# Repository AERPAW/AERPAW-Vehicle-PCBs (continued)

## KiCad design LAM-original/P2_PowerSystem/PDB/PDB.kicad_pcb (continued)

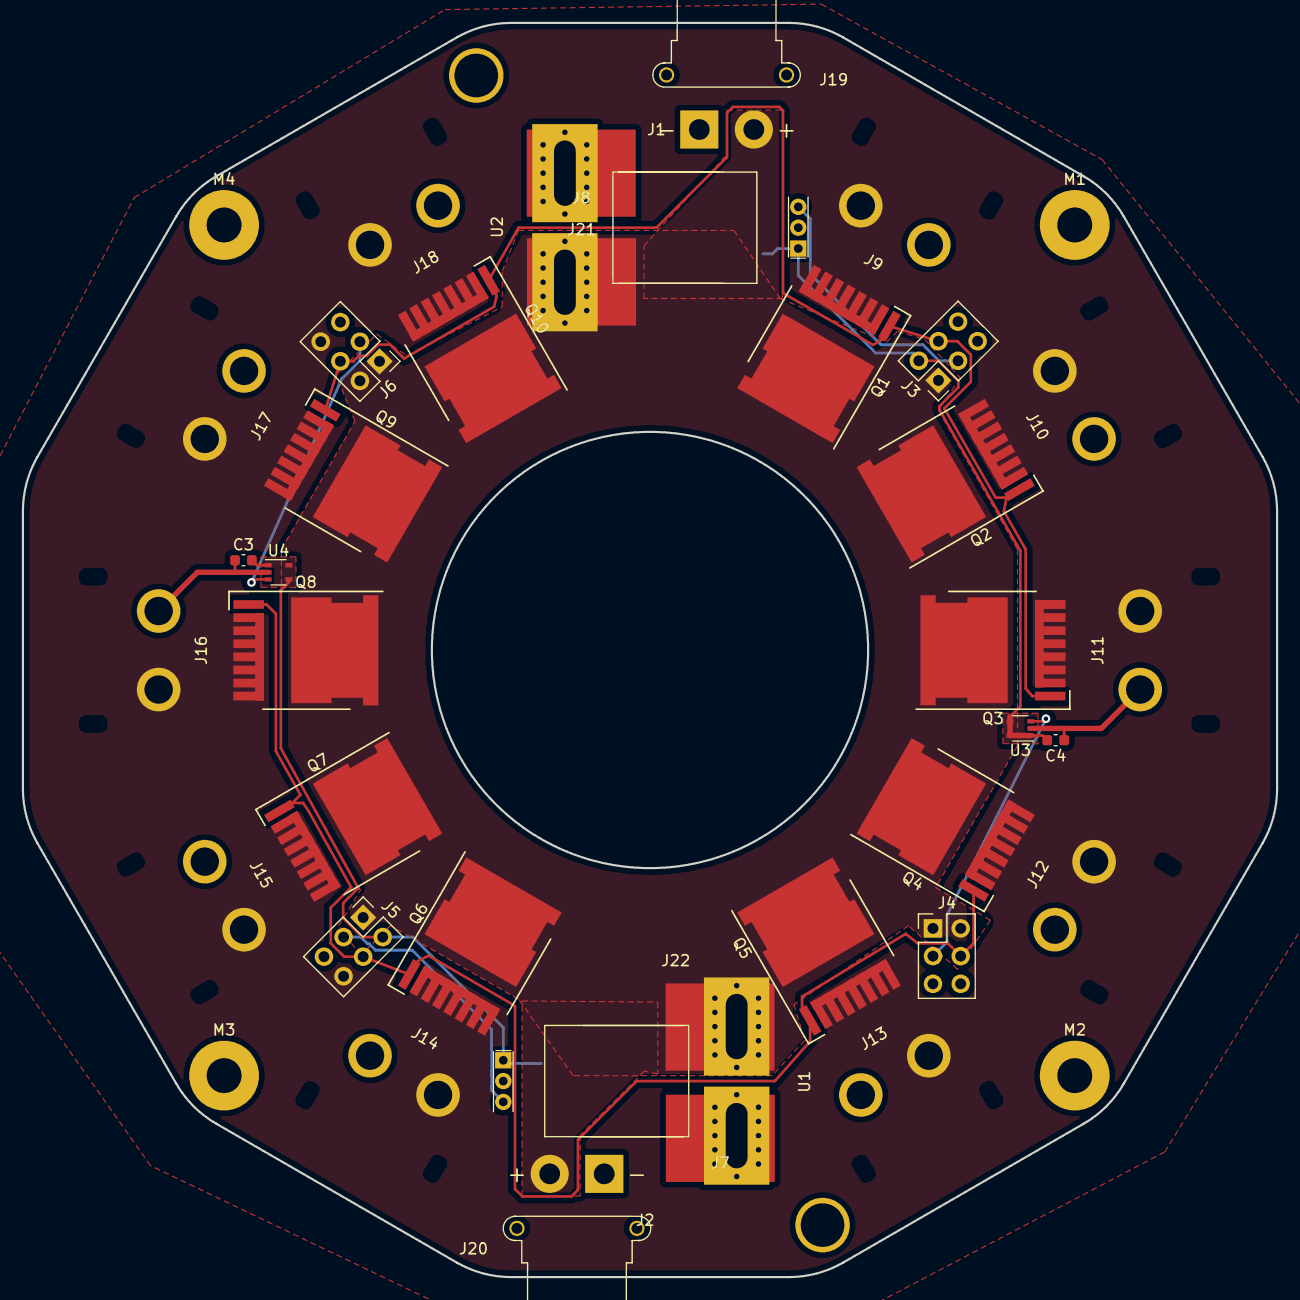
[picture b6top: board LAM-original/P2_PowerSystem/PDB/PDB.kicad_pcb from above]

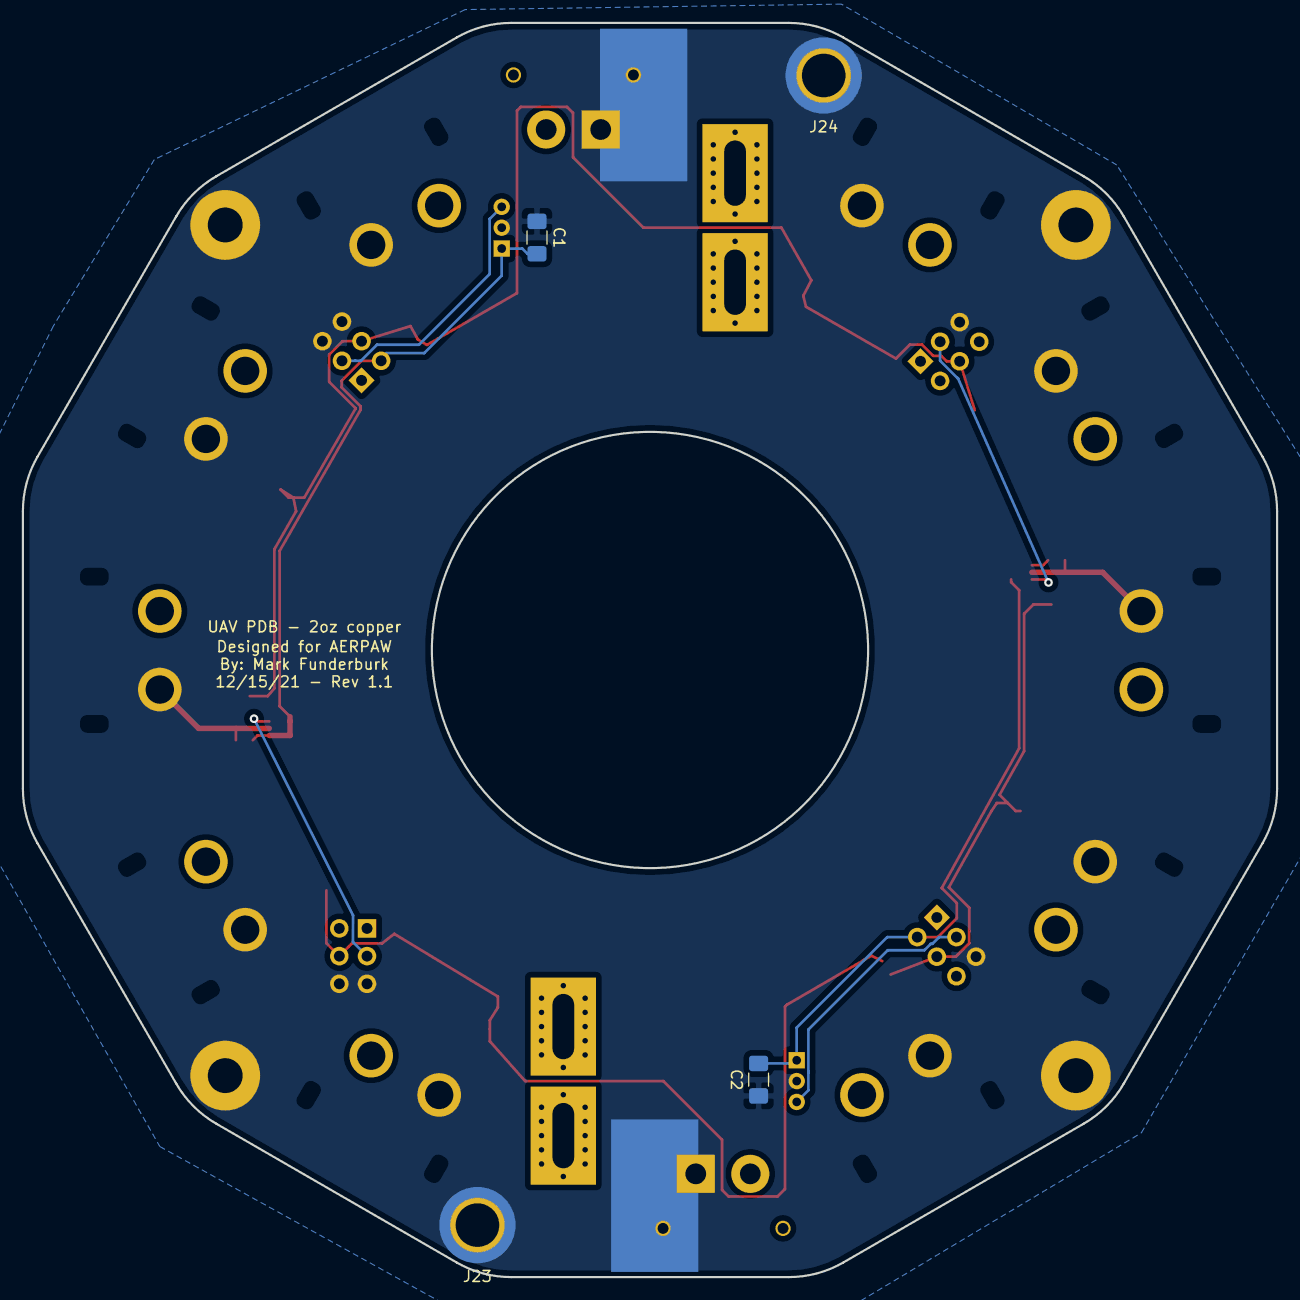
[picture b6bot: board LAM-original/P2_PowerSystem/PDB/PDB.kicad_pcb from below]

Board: 2 copper layers, 115.0 x 115.0 mm, 46 parts (4 on the bottom side), 11 nets.

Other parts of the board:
M1, M2, M3, M4: MountingHole_3.2mm_M3_Pad

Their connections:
GND: M1.1, M2.1, M3.1, M4.1; also elsewhere on the board

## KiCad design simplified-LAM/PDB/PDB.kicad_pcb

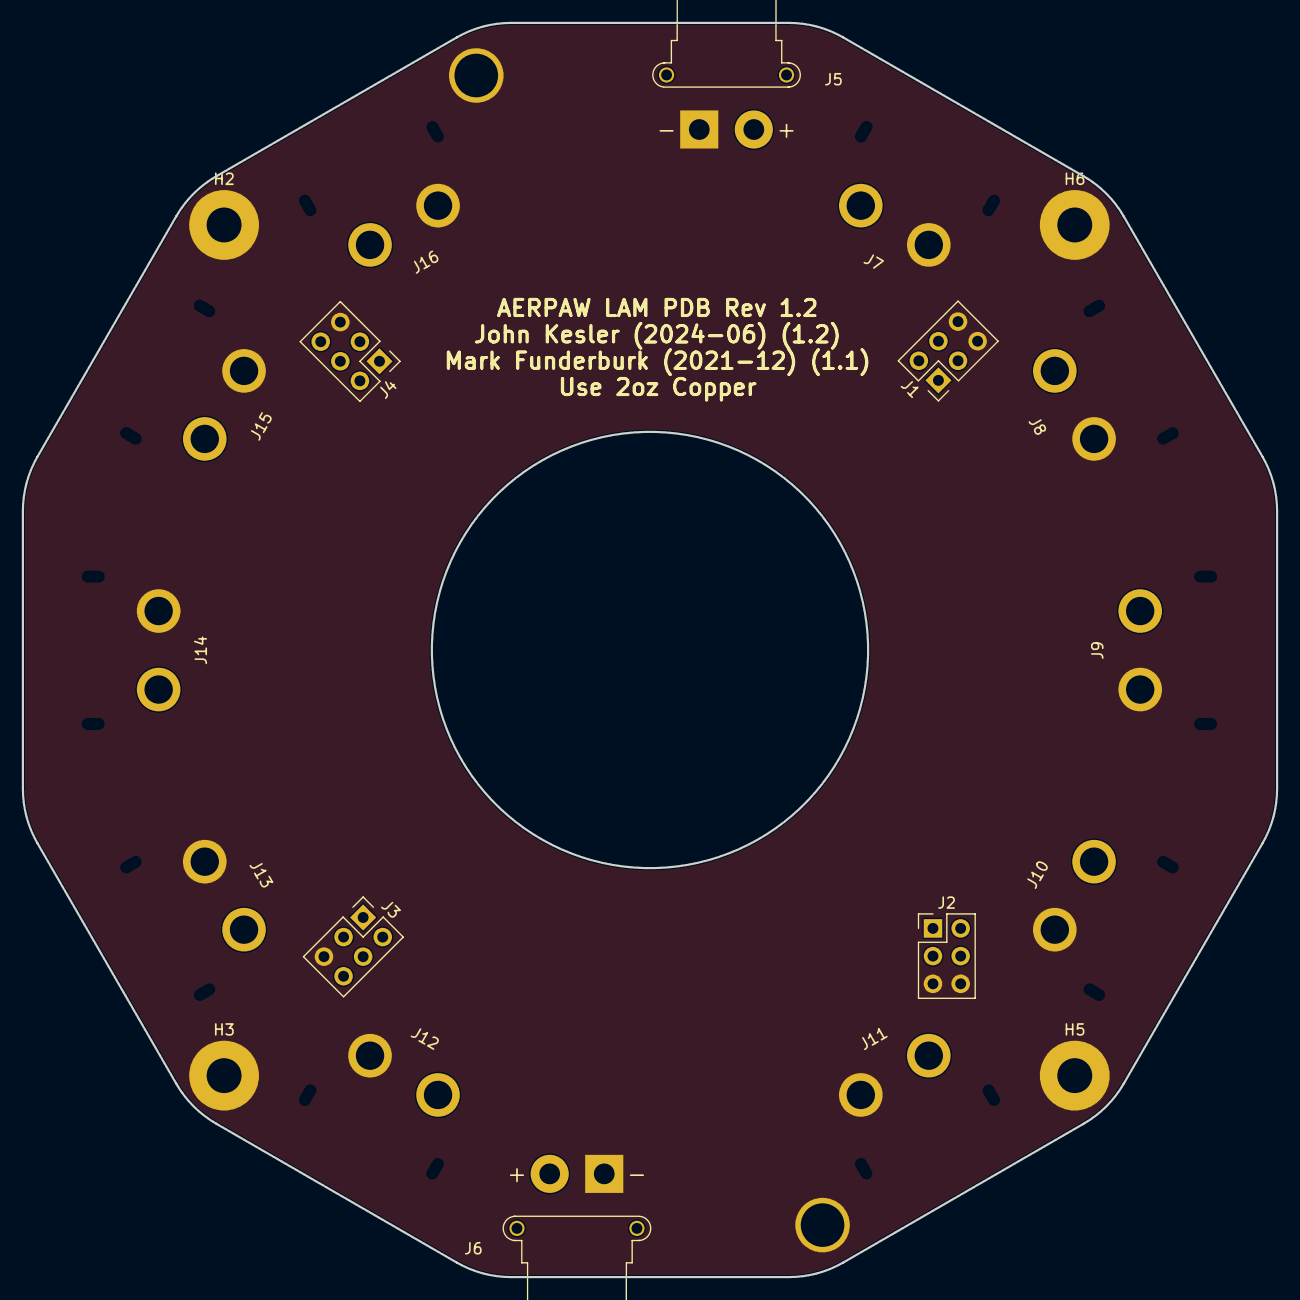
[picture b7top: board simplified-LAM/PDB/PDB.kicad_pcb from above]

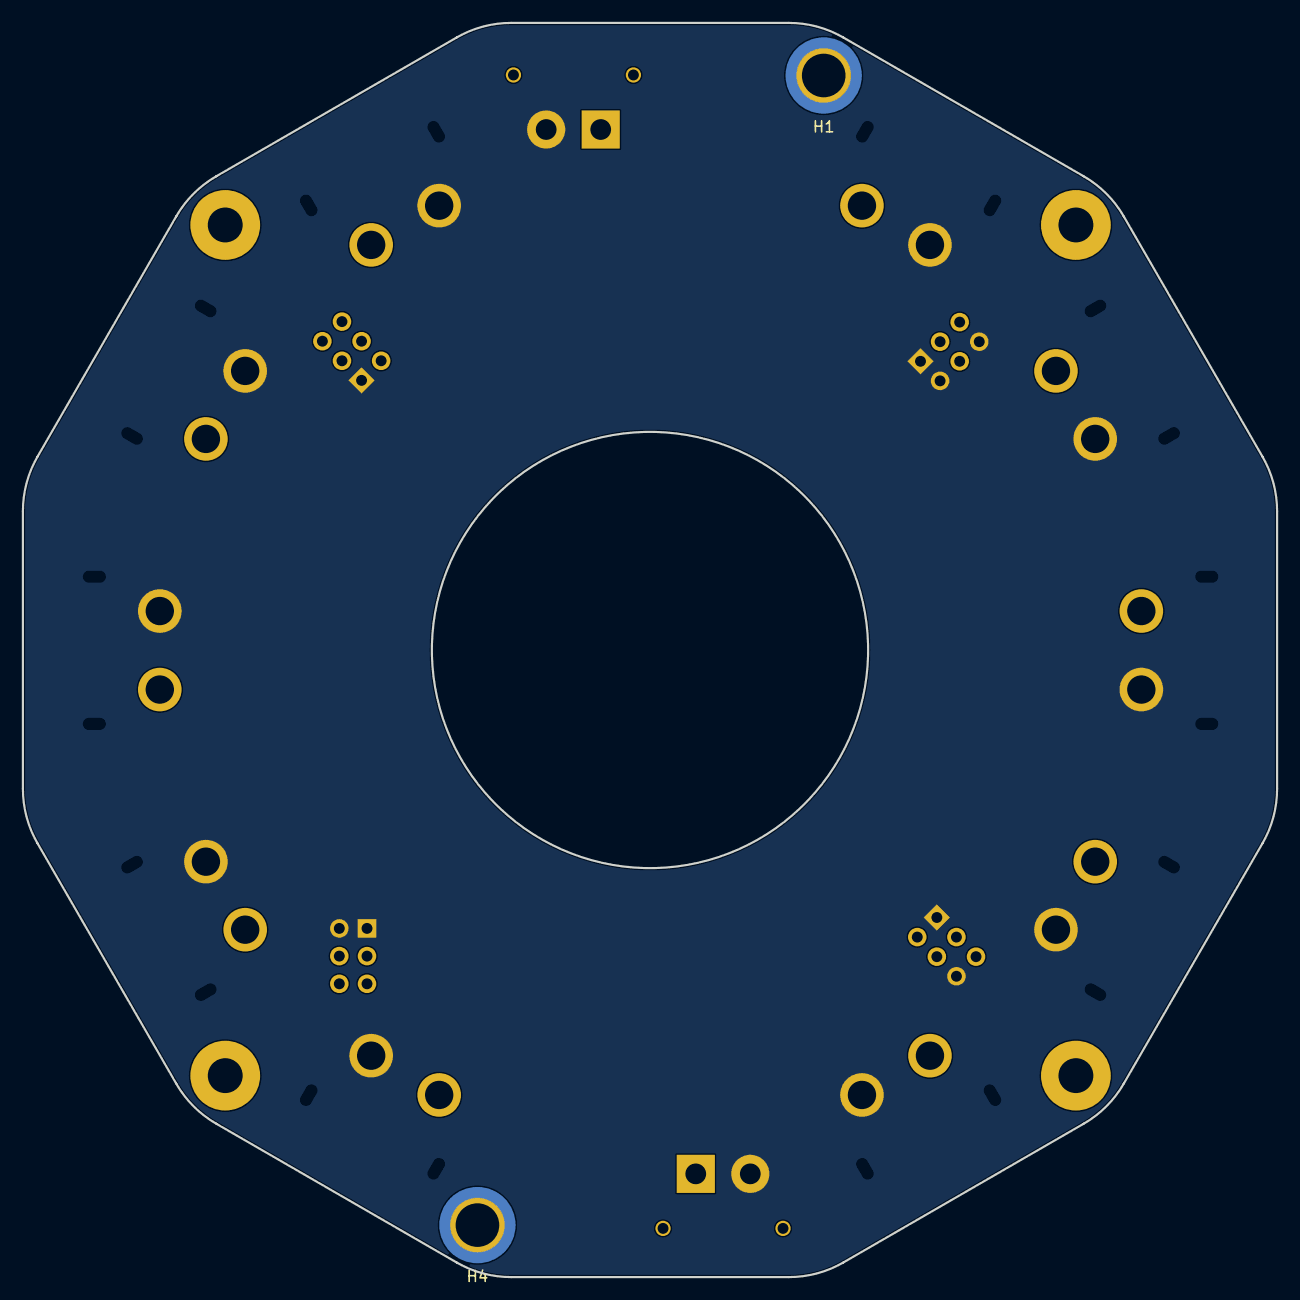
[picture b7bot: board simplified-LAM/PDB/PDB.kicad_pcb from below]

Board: 2 copper layers, 115.0 x 115.0 mm, 22 parts (2 on the bottom side), 3 nets, no tracks yet.

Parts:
H1, H4: MountingHole_Pad; MountingHole_4mm_Pad
H2, H3, H5, H6: MountingHole_Pad; MountingHole_3.2mm_M3_Pad
J1, J2, J3, J4: Conn_02x03_Counter_Clockwise; PinSocket_2x03_P2.54mm_Vertical
J5, J6: Conn_01x02; AMASS_XT30PW-F_1x02_P2.50mm_Horizontal
J7, J8, J9, J10, J11, J12, J13, J14, J15, J16: Conn_01x02; XT-60_horizontal

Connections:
+5VA: J1.2, J3.2
GND: H1.1, H2.1, H3.1, H4.1, H5.1, H6.1, J1.5, J1.6, J2.5, J2.6, J3.5, J4.5, J5.1, J6.1, J7.2, J8.2, J9.2, J10.2, J11.2, J12.2, J13.2, J14.2, J15.2, J16.2
V+_BATT: J1.1, J2.1, J2.2, J3.1, J3.6, J4.1, J4.2, J4.6, J5.2, J6.2, J7.1, J8.1, J9.1, J10.1, J11.1, J12.1, J13.1, J14.1, J15.1, J16.1

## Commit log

2024-06-13 add simplified LAM PDB PCB
2024-06-13 add JLCPCB manufacturing files for simplified LAM PDB
2024-06-13 add old LAM and SAM design files
2024-06-17 add simplified SAM board schematics
2024-06-30 add production files for EasyLAM PDB, STEP for EasySAM
2024-07-01 EasySAM fix edge clearance violations
2024-11-27 add LED board production files
2026-02-02 add 3d AMASS conns
2026-02-03 fix XT90-F footprint
2026-02-03 add BOM
2026-02-03 add 2.x revision for AS150 pdb pcbs
2026-02-03 add AS150U 3d+footprint
2026-02-03 add AS150s to PDB r2.0
2026-02-05 add jlc manufacturing files
2026-02-27 add pcb raw image processing
2026-02-27 bring footprints to parity with modern kicad
2026-02-27 reannotate sam schem to bring into parity
2026-02-27 place top. revisit missing parts
2026-03-02 add WIP step file for sam boards
2026-03-04 finalize core routing
2026-03-09 add STEP file for r1.2 SAMe + SAM carrier and power delivery board
2026-03-10 add updated SAM4 routing (DRC clean) + model
2026-03-10 reorg directories
2026-03-18 final san check routing. add protection
2026-03-18 add JLC ordering files. small tweaks
2026-06-30 update SAME connectors to better fit SAME mechanical design
